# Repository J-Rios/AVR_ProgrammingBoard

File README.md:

# AVR_ProgrammingBoard
Eagle AVR MCUs programming board for ISP-6PIN connection (AVRISP, USBASP...).
[See Image](Image.png).

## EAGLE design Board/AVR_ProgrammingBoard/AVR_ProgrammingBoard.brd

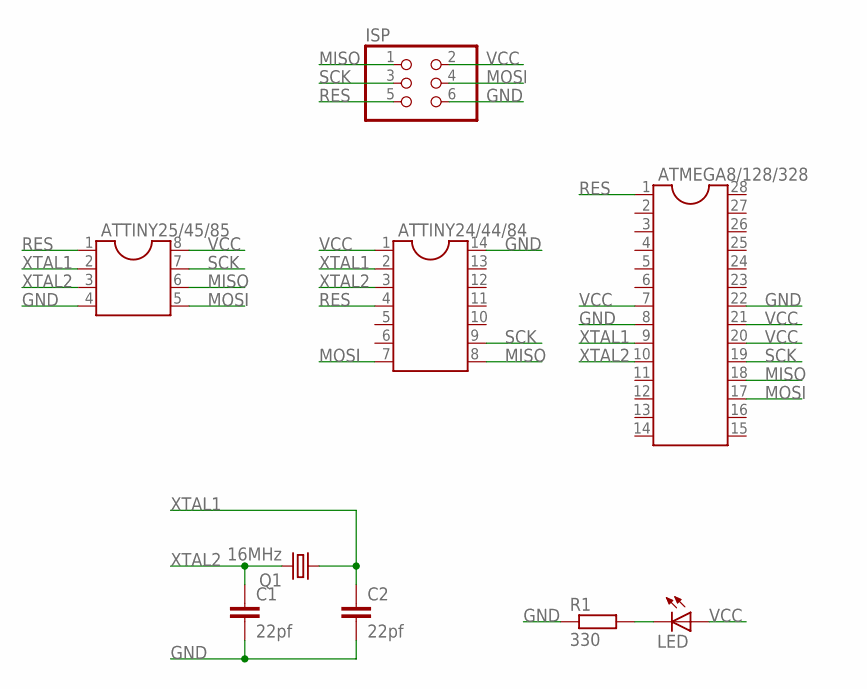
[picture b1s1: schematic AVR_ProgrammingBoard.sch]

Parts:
ATMEGA8/128/328: DIL28-3
ATTINY24/44/84: DIL14
ATTINY25/45/85: DIL8; DIL08
C1, C2: 22pf; C5B3
ISP: PINHD-2X3; 2X03
LED: LED5MM
Q1: 16MHz; HC49U-V
R1: 330; 0204/7

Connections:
GND: ATMEGA8/128/328.8, ATMEGA8/128/328.22, ATTINY24/44/84.14, ATTINY25/45/85.4, C1.2, C2.2, ISP.6, R1.1
MISO: ATMEGA8/128/328.18, ATTINY24/44/84.8, ATTINY25/45/85.6, ISP.1
MOSI: ATMEGA8/128/328.17, ATTINY24/44/84.7, ATTINY25/45/85.5, ISP.4
unnamed: LED.K (C), R1.2
RES: ATMEGA8/128/328.1, ATTINY24/44/84.4, ATTINY25/45/85.1, ISP.5
SCK: ATMEGA8/128/328.19, ATTINY24/44/84.9, ATTINY25/45/85.7, ISP.3
VCC: ATMEGA8/128/328.7, ATMEGA8/128/328.20, ATMEGA8/128/328.21, ATTINY24/44/84.1, ATTINY25/45/85.8, ISP.2, LED.A
XTAL1: ATMEGA8/128/328.9, ATTINY24/44/84.2, ATTINY25/45/85.2, C2.1, Q1.1
XTAL2: ATMEGA8/128/328.10, ATTINY24/44/84.3, ATTINY25/45/85.3, C1.1, Q1.2

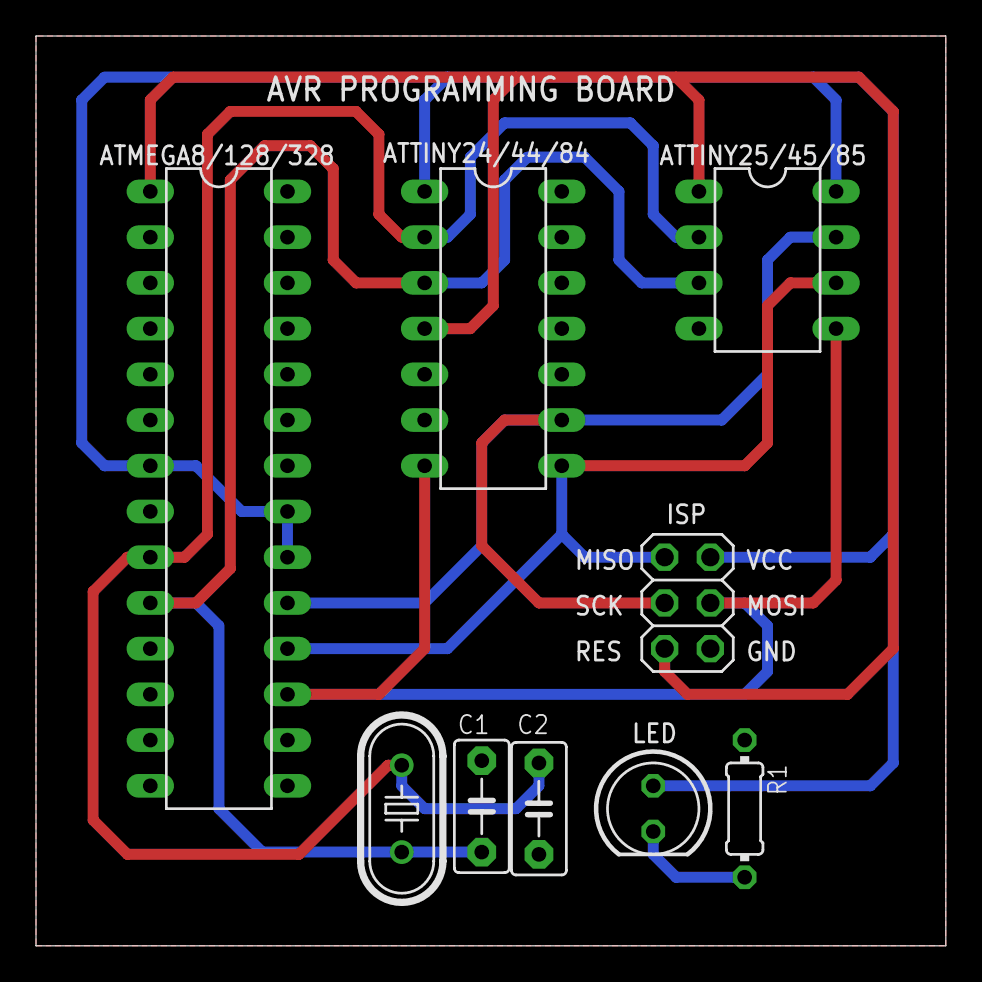
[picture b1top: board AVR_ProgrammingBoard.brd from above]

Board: 2 copper layers, 50.5 x 50.5 mm, 9 parts (0 on the bottom side), 9 nets.

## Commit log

2015-05-18 Eagle project added
    Project and image files added
